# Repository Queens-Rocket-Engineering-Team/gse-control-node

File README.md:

# GSE Control Node

The GSE control node is the control PCB for GSE systems to integrate with launch control. This includes actuator control, fan control, and a load cell reading. This control node is used for control of the GSE equipment on the launch tower.

## System Architecture

Control nodes use an ESP32S3-WROOM-1U microcontroller for systems control. This ESP32S3 communicates with an external control
server to for remote control and data streaming over 2.4GHz WiFi. All commands are sent from the external server, as
control nodes does not autonomously control any systems.

A communications diagram for the GSE control node can be seen below.

```mermaid
---
title: Communications Flow
---
flowchart LR

    ADC(ADS112C04<br>ADCs) <==I2C==> ESP(ESP32 MCU)

    subgraph Controls
        AV(Actuators)
    end

    subgraph Sensors
        LC(Load Cell)
    end

    LC --> ADC

    ESP --> AV

    ESP <-. WiFI .-> WIFI(External Server)
```

## Power Architecture

The GSE control node operates from a 24VDC power supply. The 24V rail is first stepped down to 5.17V with a switching converter and then dropped to 5V and 3.3V with LDOs. The 5V rail supplies analog systems, and the 3.3V rail supplies digital systems. Using LDOs on the switching output allows for low-noise power for analog measurements. There is also a switching converter to step the 24V rail down to 12V, to power fans.

```mermaid
---
title: Power Distribution
---
flowchart LR

    subgraph Actuators
        AV(Actuators)
    end
    24VIN --> AV

    subgraph Voltage Regulation
        BUCK_12([12V Buck])
        BUCK_5.17([5.17V Buck])
        BUCK_5.17 --> 5V([5V LDO])
        BUCK_5.17 --> 3V3([3.3V LDO])
    end

    24VIN --> BUCK_12
    24VIN --> BUCK_5.17

    subgraph Fans
        FANS(Fans)
    end

    subgraph Sensors
        LC(Load Cell)
    end

    BUCK_12 ---> FANS
    5V --> ADC(ADS112C04<br>ADCs)
    3V3 --> ESP(ESP32 MCU)
    3V3 --> ADC
    5V --> LC
```

## Required Software

This project was created using KiCad v10.0. If manufacturing with JLCPCB, install the Fabrication Toolkit KiCad plugin for JLCPCB.

## Recommended Manufacturing Options

If ordering from JLCPCB, use the JLC04161H-3313 stackup option. For JLC PCBA, the standard PCBA option is required due
to the ESP32S3-WROOM-1U being unavailable as a part in the economic PCBA assembly.

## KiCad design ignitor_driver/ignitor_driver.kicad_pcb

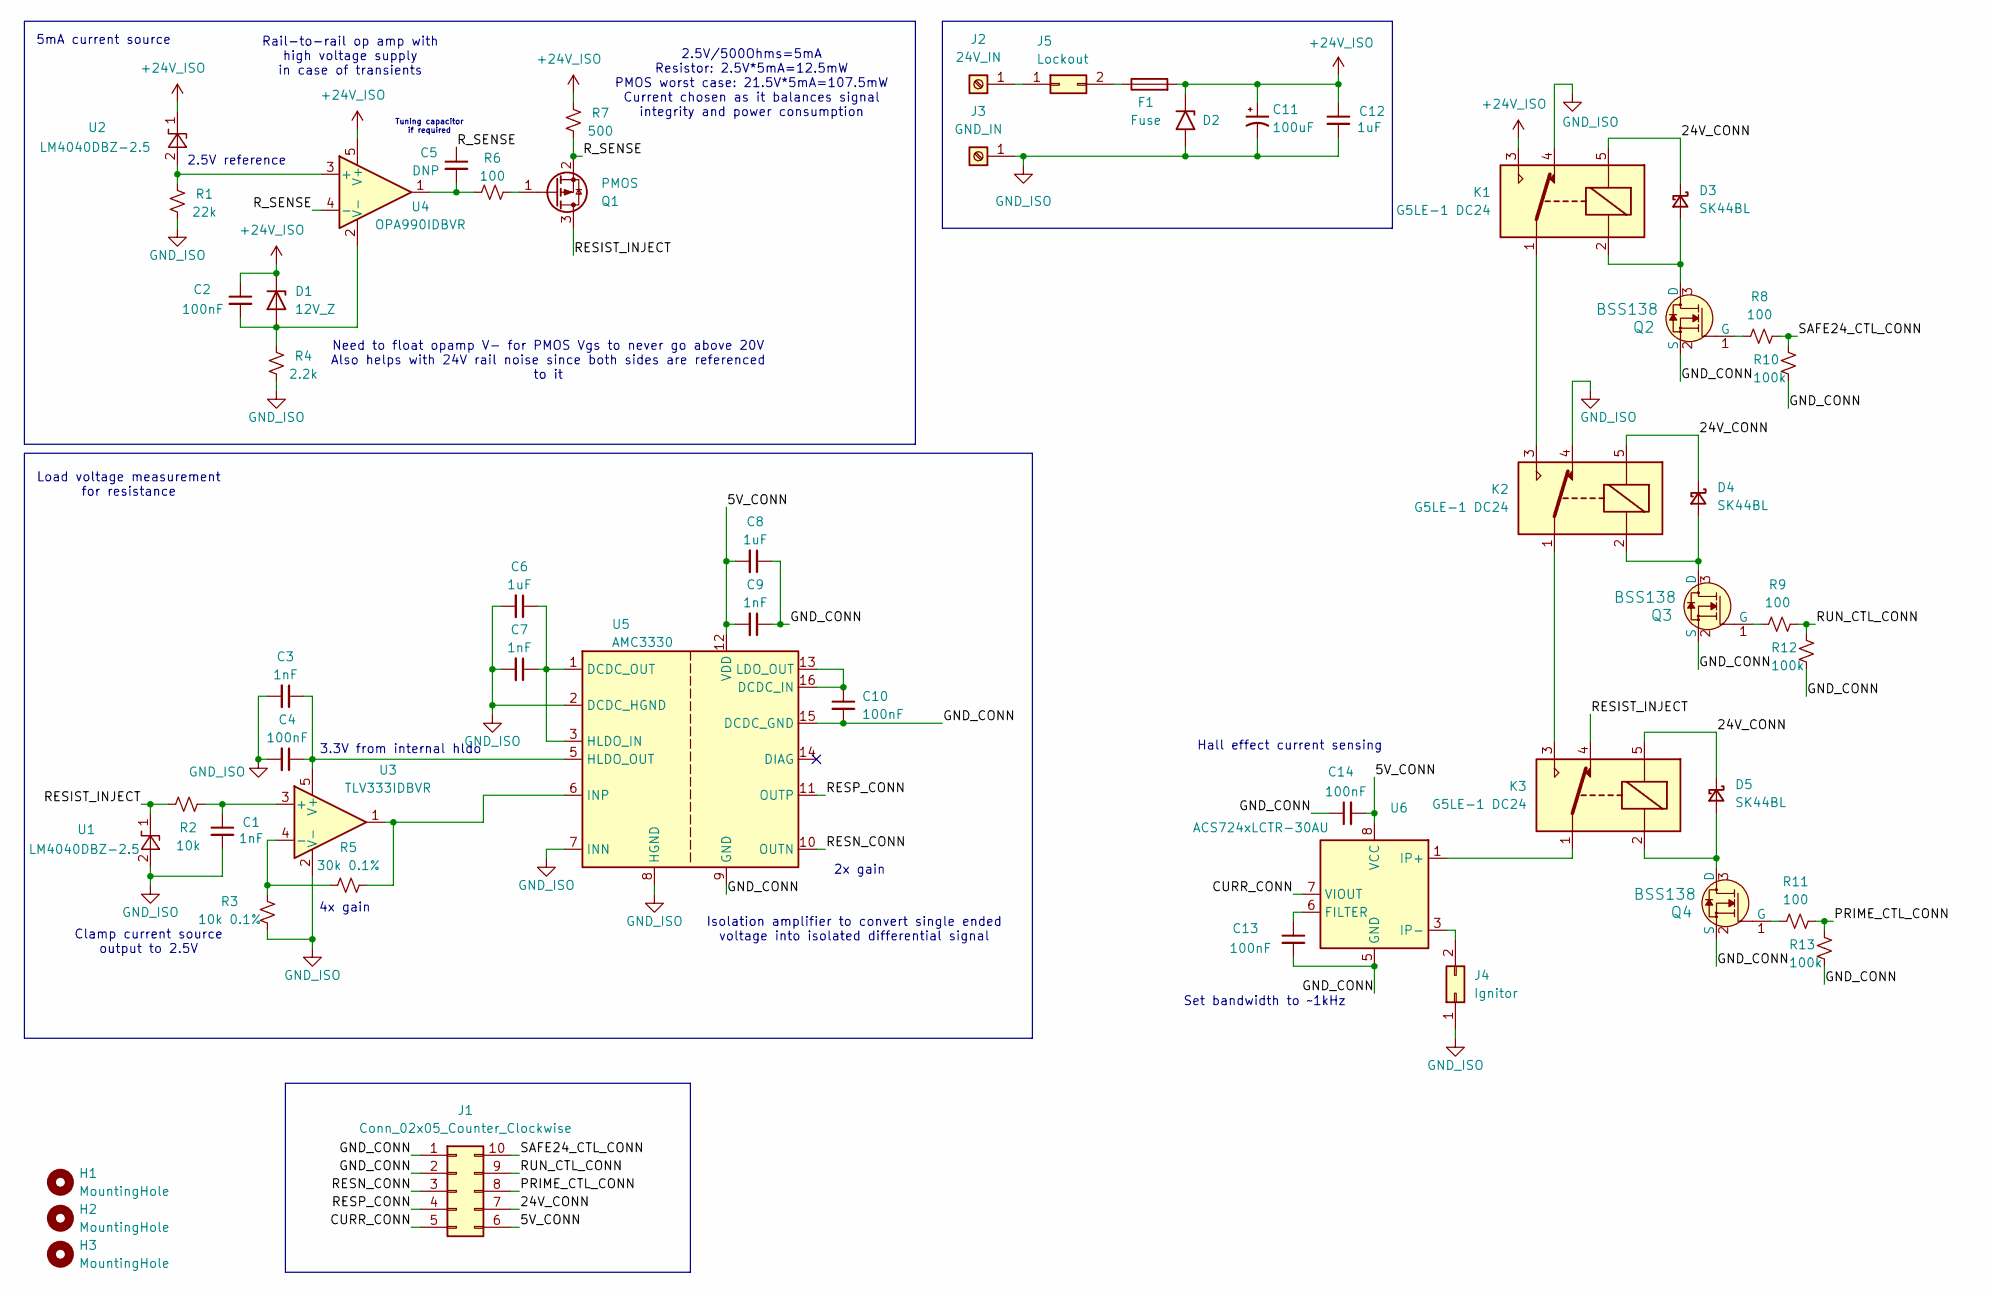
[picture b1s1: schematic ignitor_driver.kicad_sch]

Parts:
C1, C3, C7, C9: 1nF; C_0805_2012Metric_Pad1.18x1.45mm_HandSolder
C2, C4, C10, C13, C14: 100nF; C_0805_2012Metric_Pad1.18x1.45mm_HandSolder
C5: DNP; C_0805_2012Metric_Pad1.18x1.45mm_HandSolder
C6, C8, C12: 1uF; C_0805_2012Metric_Pad1.18x1.45mm_HandSolder
C11: 100uF; CP_Radial_D8.0mm_P5.00mm; MPN EEU-FR1H101B
D1: 12V_Z; D_SOD-123; MPN BZT52C12-13-F
D2: SMCJ26A-13-F; D_SMC; MPN SMCJ26A
D3, D4, D5: SK44BL; D_SMB_Handsoldering; MPN SK44BL-TP
F1: Fuse; Fuseholder_Blade_Mini_Keystone_3568
H1, H2, H3: MountingHole; MountingHole_3.2mm_M3
J1: Conn_02x05_Counter_Clockwise; Molex_Micro-Fit_3.0_43045-1012_2x05_P3.00mm_Vertical
J2: 24V_IN; AMT0440007DB0000G; MPN AMT0440007DB0000G
J3: GND_IN; AMT0440007DB0000G; MPN AMT0440007DB0000G
J4: Ignitor; Molex_Mini-Fit_Jr_5566-02A_2x01_P4.20mm_Vertical
J5: Lockout; Molex_Mini-Fit_Jr_5566-02A_2x01_P4.20mm_Vertical
K1, K2, K3: G5LE-1 DC24; Relay_SPDT_Omron-G5LE-1
Q1: PMOS; SOT-23; MPN BSS83PH6327XTSA1
Q2, Q3, Q4: BSS138; SOT-23; MPN BSS138
R1: 22k; R_0805_2012Metric_Pad1.20x1.40mm_HandSolder; MPN 0402WGF1000TCE
R2: 10k; R_0805_2012Metric_Pad1.20x1.40mm_HandSolder; MPN 0402WGF1000TCE
R3: 10k 0.1%; R_0805_2012Metric_Pad1.20x1.40mm_HandSolder; MPN 0402WGF1000TCE
R4: 2.2k; R_0805_2012Metric_Pad1.20x1.40mm_HandSolder; MPN 0402WGF1000TCE
R5: 30k 0.1%; R_0805_2012Metric_Pad1.20x1.40mm_HandSolder; MPN 0402WGF1000TCE
R6, R8, R9, R11: 100; R_0805_2012Metric_Pad1.20x1.40mm_HandSolder; MPN 0402WGF1000TCE
R7: 500; R_0603_1608Metric_Pad0.98x0.95mm_HandSolder; MPN 0402WGF1000TCE
R10, R12, R13: 100k; R_0805_2012Metric_Pad1.20x1.40mm_HandSolder; MPN 0402WGJ0103TCE
U1, U2: LM4040DBZ-2.5; SOT-23; MPN LM4040C25FTA
U3: TLV333IDBVR; SOT-23-5_HandSoldering
U4: OPA990IDBVR; SOT-23-5_HandSoldering
U5: AMC3330; SOIC-16W_7.5x10.3mm_P1.27mm; MPN AMC3330DWER
U6: ACS724xLCTR-30AU; SOIC-8_3.9x4.9mm_P1.27mm; MPN ACS724LLCTR-30AU-T

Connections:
+24V_ISO: C2.1, C11.1, C12.1, D1.1 (K), D2.1 (A1), F1.2, K1.3, R7.1, U2.1 (K), U4.5 (V+)
/5V_CONN: C8.2, C9.2, C14.2, J1.6, U5.12 (VDD), U6.8 (VCC)
/24V_CONN: D3.1 (K), D4.1 (K), D5.1 (K), J1.7, K1.5, K2.5, K3.5
/CURR_CONN: J1.5, U6.7 (VIOUT)
/GND_CONN: C8.1, C9.1, C10.2, C13.2, C14.1, J1.1, J1.2, Q2.2 (S), Q3.2 (S), Q4.2 (S), R10.2, R12.2, R13.2, U5.9 (GND), U5.15 (DCDC_GND), U6.5 (GND)
/PRIME_CTL_CONN: J1.8, R11.2, R13.1
/RESIST_INJECT: K3.4, Q1.3 (D), R2.1, U1.1 (K)
/RESN_CONN: J1.3, U5.10 (OUTN)
/RESP_CONN: J1.4, U5.11 (OUTP)
/RUN_CTL_CONN: J1.9, R9.2, R12.1
/R_SENSE: C5.1, Q1.2 (S), R7.2, U4.4 (-)
/SAFE24_CTL_CONN: J1.10, R8.2, R10.1
GND_ISO: C1.2, C3.2, C4.2, C6.2, C7.2, C11.2, C12.2, D2.2 (A2), J3.1 (Pin_1_1), J4.1, K1.4, K2.4, R1.2, R3.1, R4.2, U1.2 (A), U3.2 (V-), U5.2 (DCDC_HGND), U5.7 (INN), U5.8 (HGND)
unnamed: C5.2, R6.1, U4.1
unnamed: C2.2, D1.2 (A), R4.1, U4.2 (V-)
unnamed: D3.2 (A), K1.2, Q2.3 (D)
unnamed: D4.2 (A), K2.2, Q3.3 (D)
unnamed: D5.2 (A), K3.2, Q4.3 (D)
unnamed: J2.1 (Pin_1_1), J5.1
unnamed: J4.2, U6.3 (IP-), U6.4 (IP-)
unnamed: F1.1, J5.2
unnamed: K1.1, K2.3
unnamed: K2.1, K3.3
unnamed: K3.1, U6.1 (IP+), U6.2 (IP+)
unnamed: Q1.1 (G), R6.2
unnamed: Q2.1 (G), R8.1
unnamed: Q3.1 (G), R9.1
unnamed: Q4.1 (G), R11.1
unnamed: R1.1, U2.2 (A), U4.3 (+)
unnamed: C1.1, R2.2, U3.3 (+)
unnamed: R3.2, R5.1, U3.4 (-)
unnamed: C3.1, C4.1, U3.5 (V+), U5.5 (HLDO_OUT)
unnamed: C10.1, U5.13 (LDO_OUT), U5.16 (DCDC_IN)
unnamed: C6.1, C7.1, U5.1 (DCDC_OUT), U5.3 (HLDO_IN)
unnamed: R5.2, U3.1, U5.6 (INP)
unnamed: C13.1, U6.6 (FILTER)

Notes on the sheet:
5mA current source
Hall effect current sensing
4x gain
Clamp current source output to 2.5V
Need to float opamp V- for PMOS Vgs to never go above 20V Also helps with 24V rail noise since both sides are referenced to it
Load voltage measurement for resistance
2.5V/500Ohms=5mA Resistor: 2.5V*5mA=12.5mW PMOS worst case: 21.5V*5mA=107.5mW Current chosen as it balances signal integrity and power consumption
Rail-to-rail op amp with high voltage supply in case of transients
2x gain
Isolation amplifier to convert single ended voltage into isolated differential signal
Tuning capacitor if required
Set bandwidth to ~1kHz
2.5V reference
3.3V from internal hldo

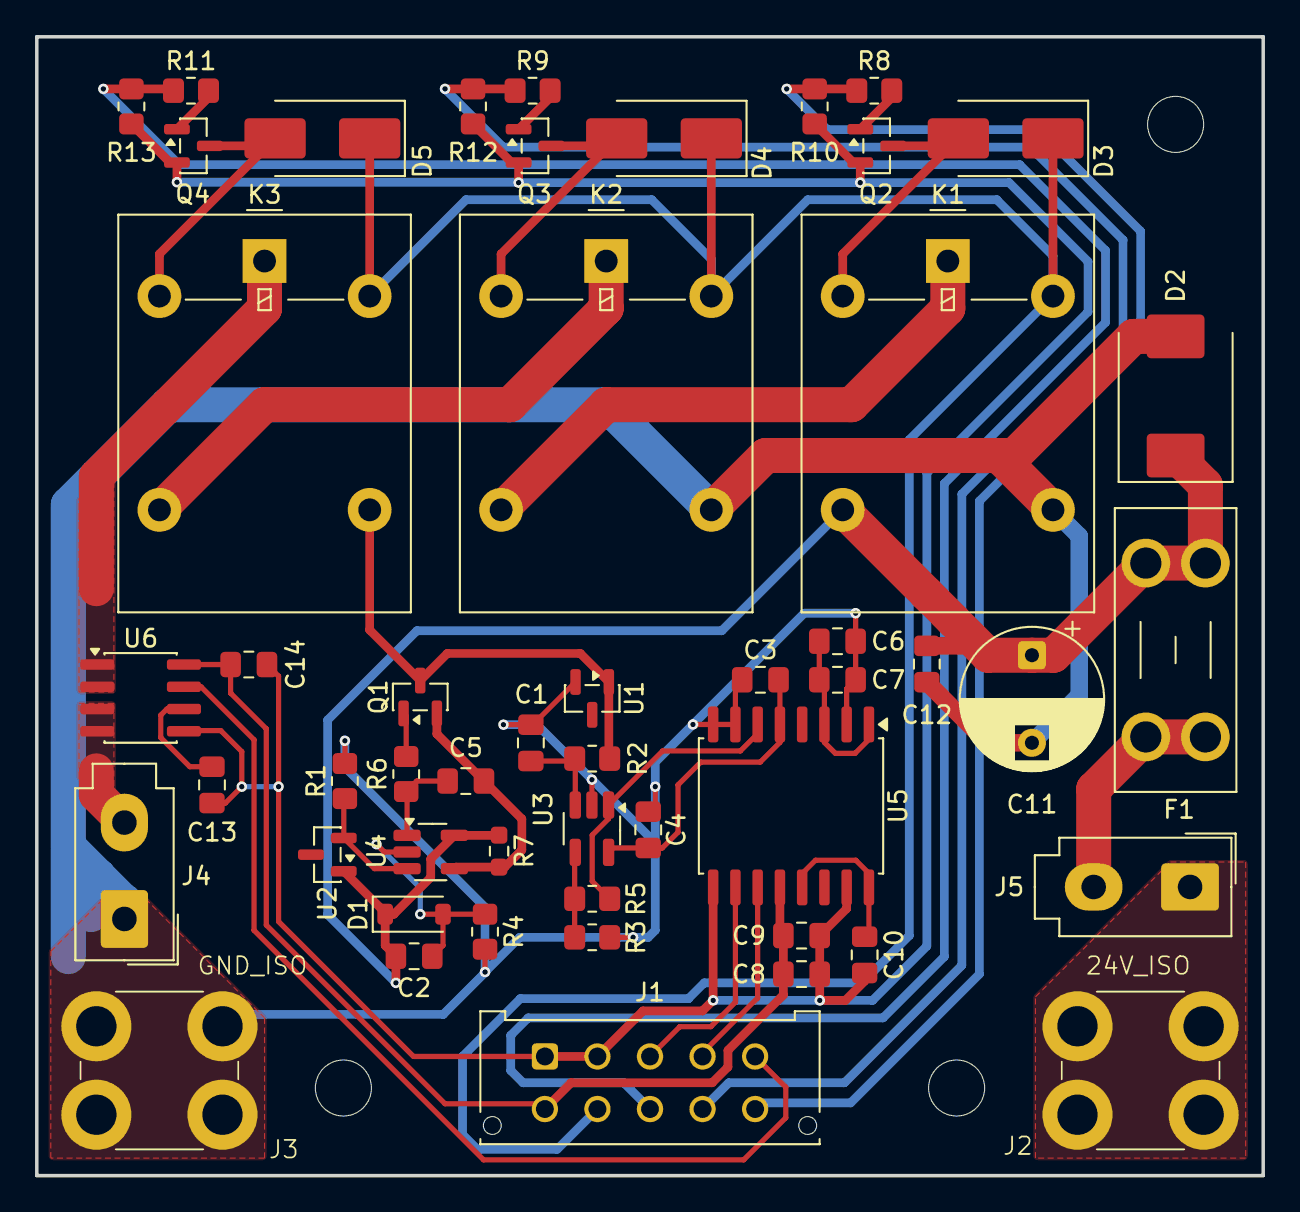
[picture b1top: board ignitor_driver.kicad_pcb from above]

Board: 2 copper layers, 70.0 x 65.0 mm, 54 parts (0 on the bottom side), 36 nets.

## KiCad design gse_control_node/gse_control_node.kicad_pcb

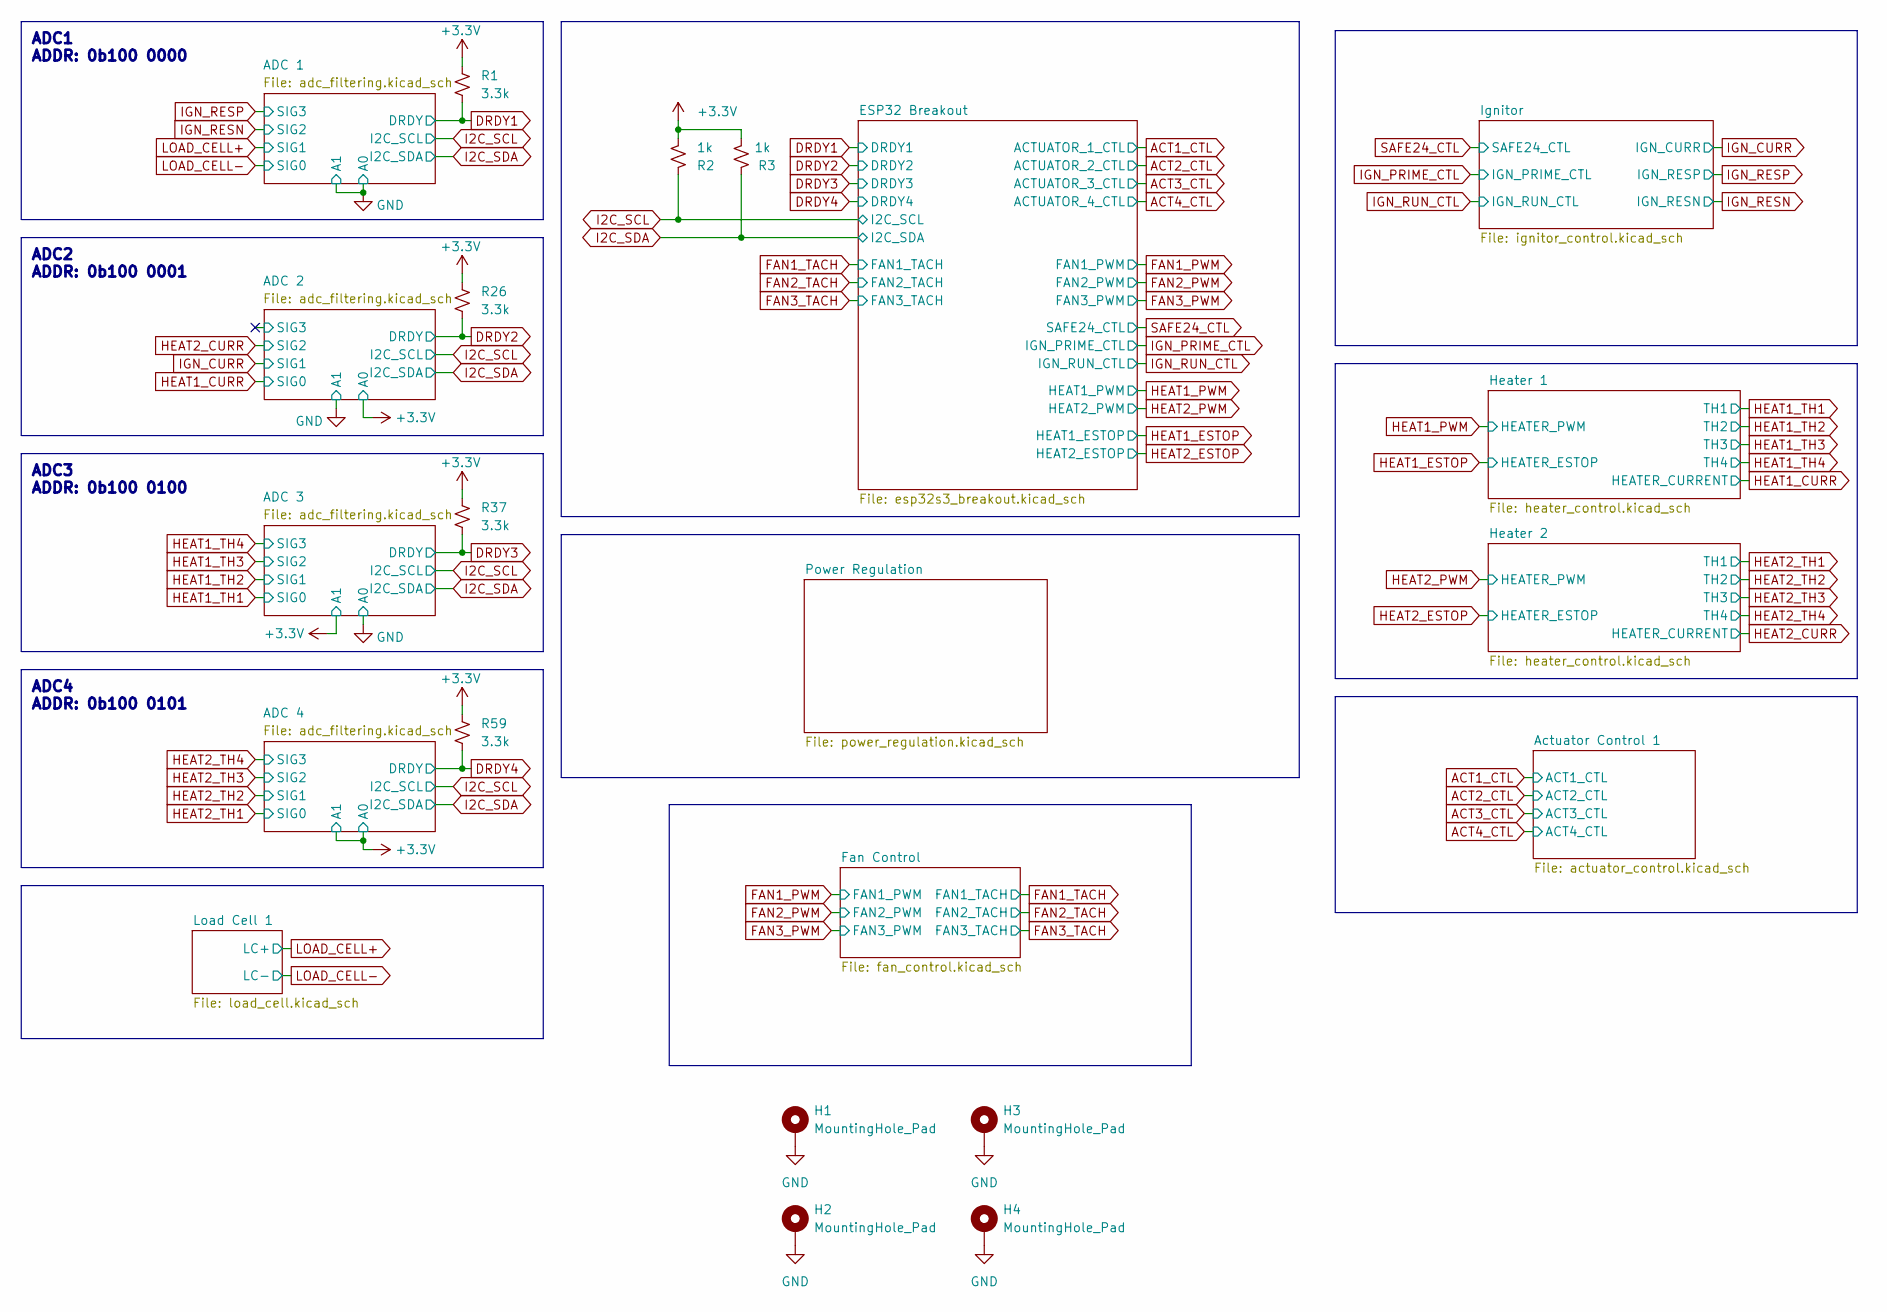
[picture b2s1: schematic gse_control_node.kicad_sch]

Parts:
H1, H2, H3, H4: MountingHole_Pad; MountingHole_3.2mm_M3_ISO7380_Pad; LCSC N/A
R1, R26, R37, R59: 3.3k; R_0603_1608Metric; LCSC C22978
R2, R3: 1k; R_0603_1608Metric; LCSC C21190

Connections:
+3.3V: R1.1, R2.2, R3.2, R26.1, R37.1, R59.1; also elsewhere on the board
DRDY1: R1.2; also elsewhere on the board
DRDY2: R26.2; also elsewhere on the board
DRDY3: R37.2; also elsewhere on the board
DRDY4: R59.2; also elsewhere on the board
GND: H1.1 (1_1), H2.1 (1_1), H3.1 (1_1), H4.1 (1_1); also elsewhere on the board
I2C_SCL: R2.1; also elsewhere on the board
I2C_SDA: R3.1; also elsewhere on the board

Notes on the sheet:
ADC2 ADDR: 0b100 0001
ADC4 ADDR: 0b100 0101
ADC1 ADDR: 0b100 0000
ADC3 ADDR: 0b100 0100

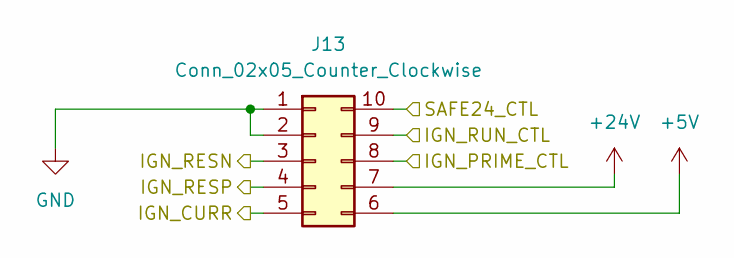
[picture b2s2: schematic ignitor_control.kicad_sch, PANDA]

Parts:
J13: Conn_02x05_Counter_Clockwise; Molex_Micro-Fit_3.0_43045-1012_2x05_P3.00mm_Vertical

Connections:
+5V: J13.6; also elsewhere on the board
+24V: J13.7; also elsewhere on the board
GND: J13.1, J13.2; also elsewhere on the board
IGN_CURR: J13.5; also elsewhere on the board
IGN_PRIME_CTL: J13.8; also elsewhere on the board
IGN_RESN: J13.3; also elsewhere on the board
IGN_RESP: J13.4; also elsewhere on the board
IGN_RUN_CTL: J13.9; also elsewhere on the board
SAFE24_CTL: J13.10; also elsewhere on the board

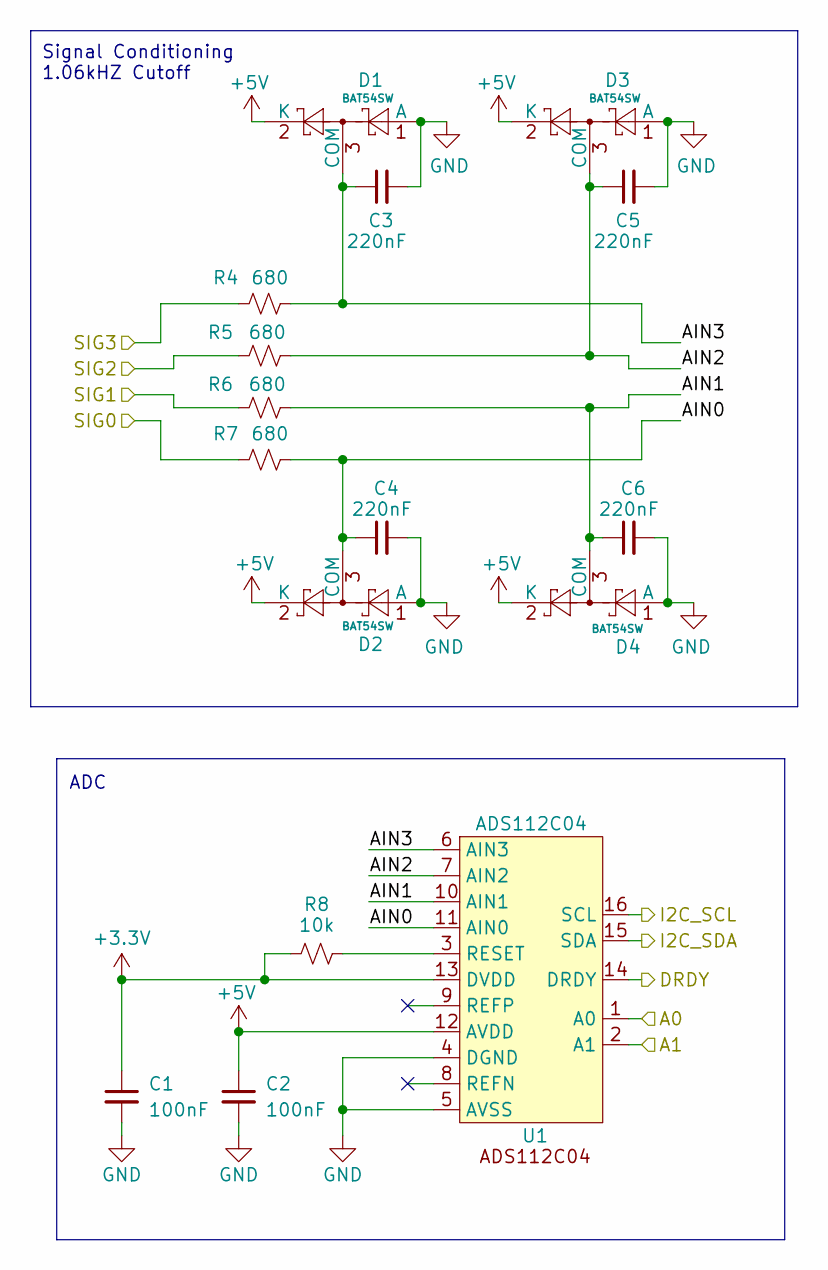
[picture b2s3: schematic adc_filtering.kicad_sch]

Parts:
C1, C2: 100nF; C_0402_1005Metric; LCSC C307331
C3, C4, C5, C6: 220nF; C_0402_1005Metric; LCSC C16772
D1, D2, D3, D4: BAT54SW; SOT-323_SC-70; LCSC C83575
R4, R5, R6, R7: 680; R_0603_1608Metric; LCSC C23228
R8: 10k; R_0603_1608Metric; LCSC C25804
U1: ADS112C04; TSSOP-16_4.4x5mm_P0.65mm; LCSC C701615

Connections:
+3.3V: C1.1, R8.1, U1.13 (DVDD); also elsewhere on the board
+5V: C2.1, D1.2 (K), D2.2 (K), D3.2 (K), D4.2 (K), U1.12 (AVDD); also elsewhere on the board
/ADC 1/AIN0: C4.1, D2.3 (COM), R7.2, U1.11 (AIN0)
/ADC 1/AIN1: C6.1, D4.3 (COM), R6.2, U1.10 (AIN1)
/ADC 1/AIN2: C5.1, D3.3 (COM), R5.2, U1.7 (AIN2)
/ADC 1/AIN3: C3.1, D1.3 (COM), R4.2, U1.6 (AIN3)
DRDY1: U1.14 (DRDY); also elsewhere on the board
GND: C1.2, C2.2, C3.2, C4.2, C5.2, C6.2, D1.1 (A), D2.1 (A), D3.1 (A), D4.1 (A), U1.1 (A0), U1.2 (A1), U1.4 (DGND), U1.5 (AVSS); also elsewhere on the board
I2C_SCL: U1.16 (SCL); also elsewhere on the board
I2C_SDA: U1.15 (SDA); also elsewhere on the board
IGN_RESN: R5.1; also elsewhere on the board
IGN_RESP: R4.1; also elsewhere on the board
LOAD_CELL+: R6.1; also elsewhere on the board
LOAD_CELL-: R7.1; also elsewhere on the board
unnamed: R8.2, U1.3 (RESET)

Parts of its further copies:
C37, C38, C43, C44, C49, C50: 100nF; C_0402_1005Metric; LCSC C307331
C39, C40, C41, C42, C45, C46, C47, C48, C51, C52, C53, C54: 220nF; C_0402_1005Metric; LCSC C16772
D12, D13, D14, D16, D17, D18, D20, D21, D22, D24, D25, D26: BAT54SW; SOT-323_SC-70; LCSC C83575
R27, R28, R29, R30, R49, R50, R51, R55, R60, R61, R62, R63: 680; R_0603_1608Metric; LCSC C23228
R31, R56, R64: 10k; R_0603_1608Metric; LCSC C25804
U8, U9, U10: ADS112C04; TSSOP-16_4.4x5mm_P0.65mm; LCSC C701615

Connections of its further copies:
+3.3V: C37.1, C43.1, C49.1, R31.1, R56.1, R64.1, U8.1 (A0), U8.13 (DVDD), U9.2 (A1), U9.13 (DVDD), U10.1 (A0), U10.2 (A1), U10.13 (DVDD); also elsewhere on the board
+5V: C38.1, C44.1, C50.1, D12.2 (K), D13.2 (K), D14.2 (K), D16.2 (K), D17.2 (K), D18.2 (K), D20.2 (K), D21.2 (K), D22.2 (K), D24.2 (K), D25.2 (K), D26.2 (K), U8.12 (AVDD), U9.12 (AVDD), U10.12 (AVDD); also elsewhere on the board
/ADC 2/AIN0: C40.1, D13.3 (COM), R30.2, U8.11 (AIN0)
/ADC 2/AIN1: C42.1, D16.3 (COM), R29.2, U8.10 (AIN1)
/ADC 2/AIN2: C41.1, D14.3 (COM), R28.2, U8.7 (AIN2)
/ADC 2/AIN3: C39.1, D12.3 (COM), R27.2, U8.6 (AIN3)
/ADC 2/SIG3: R27.1
/ADC 3/AIN0: C46.1, D18.3 (COM), R55.2, U9.11 (AIN0)
/ADC 3/AIN1: C48.1, D21.3 (COM), R51.2, U9.10 (AIN1)
/ADC 3/AIN2: C47.1, D20.3 (COM), R50.2, U9.7 (AIN2)
/ADC 3/AIN3: C45.1, D17.3 (COM), R49.2, U9.6 (AIN3)
/ADC 4/AIN0: C52.1, D24.3 (COM), R63.2, U10.11 (AIN0)
/ADC 4/AIN1: C54.1, D26.3 (COM), R62.2, U10.10 (AIN1)
/ADC 4/AIN2: C53.1, D25.3 (COM), R61.2, U10.7 (AIN2)
/ADC 4/AIN3: C51.1, D22.3 (COM), R60.2, U10.6 (AIN3)
DRDY2: U8.14 (DRDY); also elsewhere on the board
DRDY3: U9.14 (DRDY); also elsewhere on the board
DRDY4: U10.14 (DRDY); also elsewhere on the board
GND: C37.2, C38.2, C39.2, C40.2, C41.2, C42.2, C43.2, C44.2, C45.2, C46.2, C47.2, C48.2, C49.2, C50.2, C51.2, C52.2, C53.2, C54.2, D12.1 (A), D13.1 (A), D14.1 (A), D16.1 (A), D17.1 (A), D18.1 (A), D20.1 (A), D21.1 (A), D22.1 (A), D24.1 (A), D25.1 (A), D26.1 (A), U8.2 (A1), U8.4 (DGND), U8.5 (AVSS), U9.1 (A0), U9.4 (DGND), U9.5 (AVSS), U10.4 (DGND), U10.5 (AVSS); also elsewhere on the board
HEAT1_CURR: R30.1; also elsewhere on the board
HEAT1_TH1: R55.1; also elsewhere on the board
HEAT1_TH2: R51.1; also elsewhere on the board
HEAT1_TH3: R50.1; also elsewhere on the board
HEAT1_TH4: R49.1; also elsewhere on the board
HEAT2_CURR: R28.1; also elsewhere on the board
HEAT2_TH1: R63.1; also elsewhere on the board
HEAT2_TH2: R62.1; also elsewhere on the board
HEAT2_TH3: R61.1; also elsewhere on the board
HEAT2_TH4: R60.1; also elsewhere on the board
I2C_SCL: U8.16 (SCL), U9.16 (SCL), U10.16 (SCL); also elsewhere on the board
I2C_SDA: U8.15 (SDA), U9.15 (SDA), U10.15 (SDA); also elsewhere on the board
IGN_CURR: R29.1; also elsewhere on the board
unnamed: R31.2, U8.3 (RESET)
unnamed: R56.2, U9.3 (RESET)
unnamed: R64.2, U10.3 (RESET)

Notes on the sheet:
ADC
Signal Conditioning 1.06kHZ Cutoff

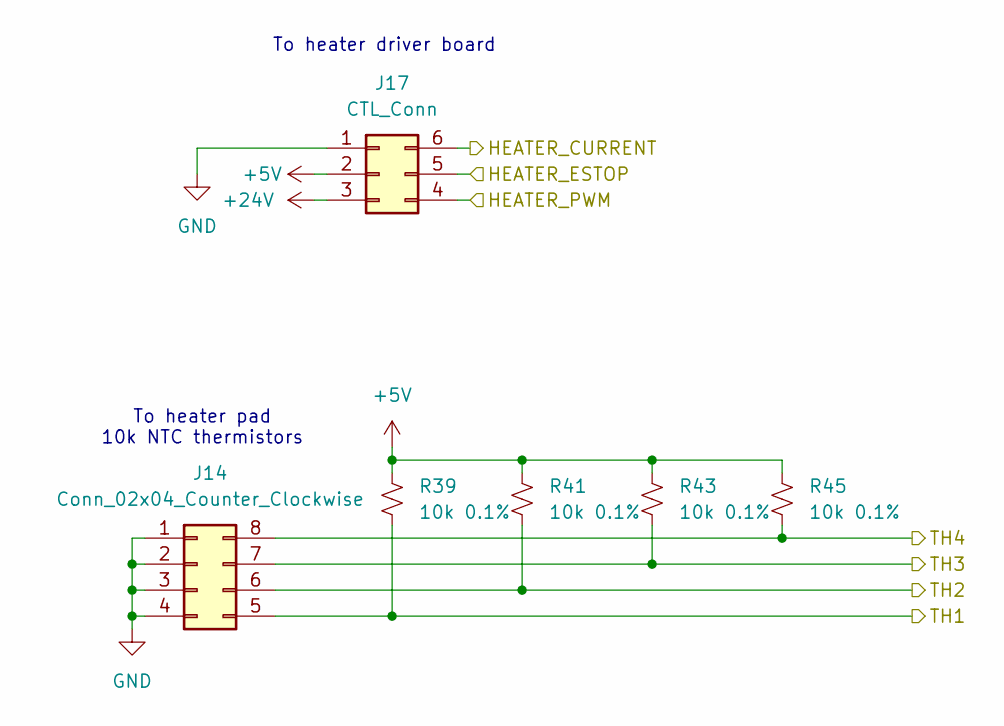
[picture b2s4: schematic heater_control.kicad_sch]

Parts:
J14: Conn_02x04_Counter_Clockwise; Molex_Micro-Fit_3.0_43045-0812_2x04_P3.00mm_Vertical
J17: CTL_Conn; Molex_Micro-Fit_3.0_43045-0612_2x03_P3.00mm_Vertical
R39, R41, R43, R45: 10k 0.1%; R_0603_1608Metric

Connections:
+5V: J17.2, R39.1, R41.1, R43.1, R45.1; also elsewhere on the board
+24V: J17.3; also elsewhere on the board
GND: J14.1, J14.2, J14.3, J14.4, J17.1; also elsewhere on the board
HEAT2_CURR: J17.6; also elsewhere on the board
HEAT2_ESTOP: J17.5; also elsewhere on the board
HEAT2_PWM: J17.4; also elsewhere on the board
HEAT2_TH1: J14.5, R39.2; also elsewhere on the board
HEAT2_TH2: J14.6, R41.2; also elsewhere on the board
HEAT2_TH3: J14.7, R43.2; also elsewhere on the board
HEAT2_TH4: J14.8, R45.2; also elsewhere on the board

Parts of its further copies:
J12: Conn_02x04_Counter_Clockwise; Molex_Micro-Fit_3.0_43045-0812_2x04_P3.00mm_Vertical
J16: CTL_Conn; Molex_Micro-Fit_3.0_43045-0612_2x03_P3.00mm_Vertical
R38, R40, R42, R44: 10k 0.1%; R_0603_1608Metric

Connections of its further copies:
+5V: J16.2, R38.1, R40.1, R42.1, R44.1; also elsewhere on the board
+24V: J16.3; also elsewhere on the board
GND: J12.1, J12.2, J12.3, J12.4, J16.1; also elsewhere on the board
HEAT1_CURR: J16.6; also elsewhere on the board
HEAT1_ESTOP: J16.5; also elsewhere on the board
HEAT1_PWM: J16.4; also elsewhere on the board
HEAT1_TH1: J12.5, R38.2; also elsewhere on the board
HEAT1_TH2: J12.6, R40.2; also elsewhere on the board
HEAT1_TH3: J12.7, R42.2; also elsewhere on the board
HEAT1_TH4: J12.8, R44.2; also elsewhere on the board

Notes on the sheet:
To heater driver board
To heater pad 10k NTC thermistors

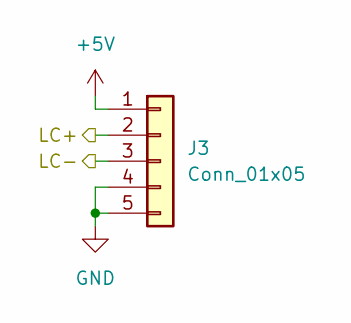
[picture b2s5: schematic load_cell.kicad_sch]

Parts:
J3: Conn_01x05; Molex_Micro-Fit_3.0_43650-0515_1x05_P3.00mm_Vertical; LCSC N/A

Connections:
+5V: J3.1; also elsewhere on the board
GND: J3.4, J3.5; also elsewhere on the board
LOAD_CELL+: J3.2; also elsewhere on the board
LOAD_CELL-: J3.3; also elsewhere on the board

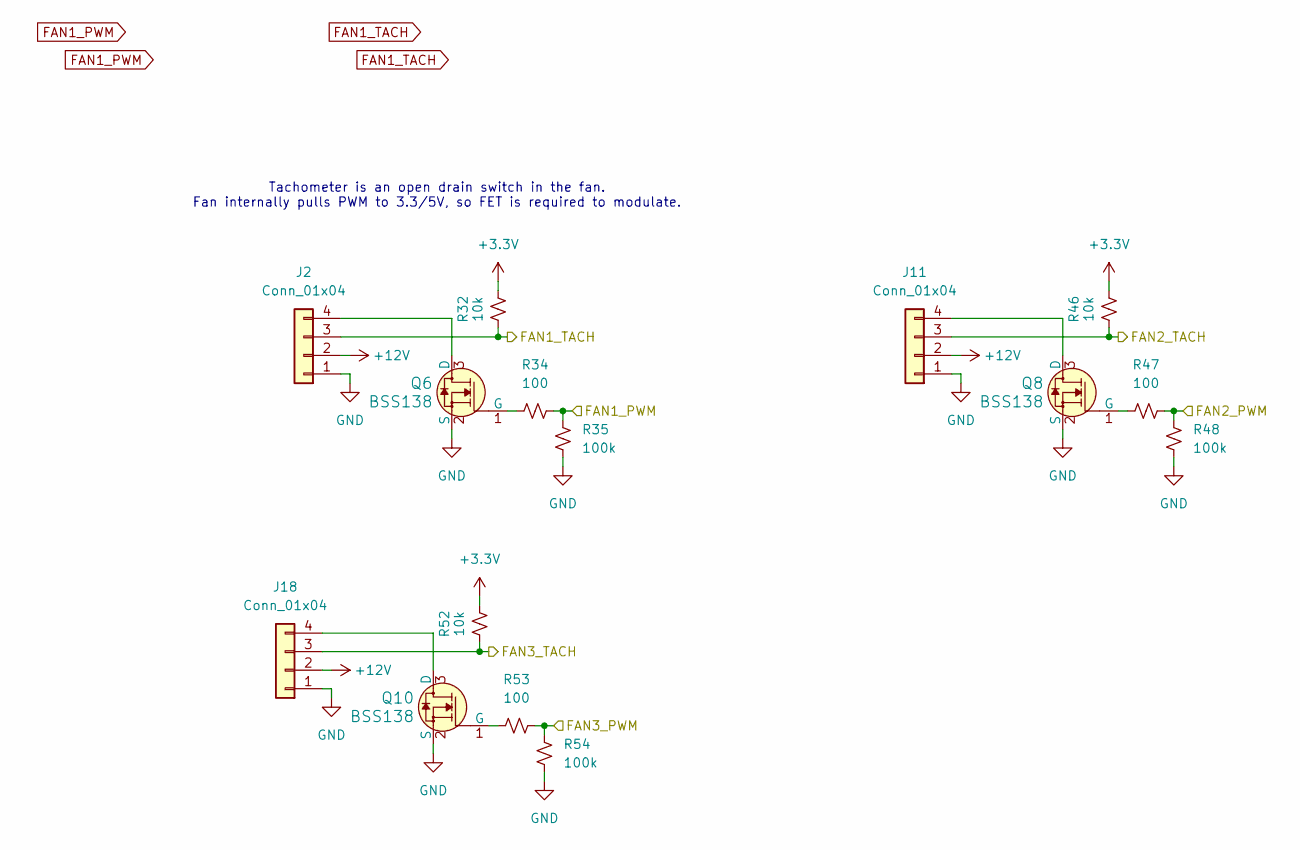
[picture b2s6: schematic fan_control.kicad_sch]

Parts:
J2, J11, J18: Conn_01x04; Molex_KK-254_AE-6410-04A_1x04_P2.54mm_Vertical; LCSC N/A
Q6, Q8, Q10: BSS138; SOT-23-3; LCSC C82045
R32, R46, R52: 10k; R_0603_1608Metric; LCSC C25804
R34, R47, R53: 100; R_0603_1608Metric
R35, R48, R54: 100k; R_0603_1608Metric; LCSC C122538

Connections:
+3.3V: R32.2, R46.2, R52.2; also elsewhere on the board
+12V: J2.2, J11.2, J18.2; also elsewhere on the board
FAN1_PWM: R34.2, R35.1; also elsewhere on the board
FAN1_TACH: J2.3, R32.1; also elsewhere on the board
FAN2_PWM: R47.2, R48.1; also elsewhere on the board
FAN2_TACH: J11.3, R46.1; also elsewhere on the board
FAN3_PWM: R53.2, R54.1; also elsewhere on the board
FAN3_TACH: J18.3, R52.1; also elsewhere on the board
GND: J2.1, J11.1, J18.1, Q6.2 (S), Q8.2 (S), Q10.2 (S), R35.2, R48.2, R54.2; also elsewhere on the board
unnamed: J2.4, Q6.3 (D)
unnamed: J11.4, Q8.3 (D)
unnamed: J18.4, Q10.3 (D)
unnamed: Q6.1 (G), R34.1
unnamed: Q8.1 (G), R47.1
unnamed: Q10.1 (G), R53.1

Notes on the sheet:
Tachometer is an open drain switch in the fan. Fan internally pulls PWM to 3.3/5V, so FET is required to modulate.

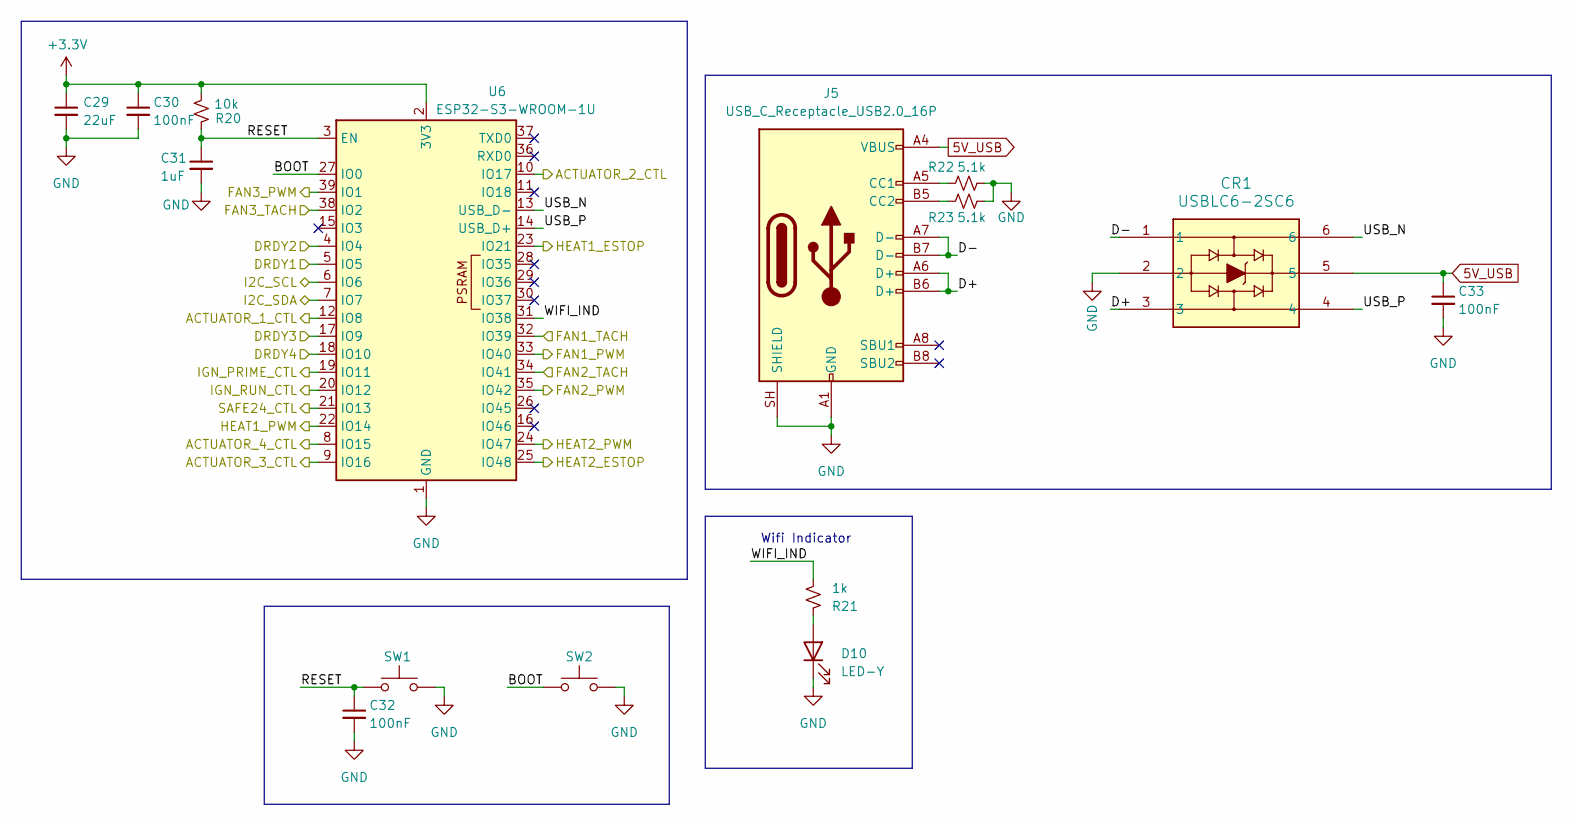
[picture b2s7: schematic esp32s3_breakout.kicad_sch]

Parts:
C29: 22uF; C_0805_2012Metric; LCSC C45783
C30, C32, C33: 100nF; C_0402_1005Metric; LCSC C307331
C31: 1uF; C_0603_1608Metric; LCSC C15849
CR1: USBLC6-2SC6; SOT-23-6; LCSC C7519
D10: LED-Y; LED_0805_2012Metric; LCSC C2296
J5: USB_C_Receptacle_USB2.0_16P; USB_C_Receptacle_G-Switch_GT-USB-7051x; LCSC C2843970
R20: 10k; R_0603_1608Metric; LCSC C25804
R21: 1k; R_0603_1608Metric; LCSC C21190
R22, R23: 5.1k; R_0603_1608Metric
SW1, SW2: USAKRO UK-B0227-G4.3-B-250; SW_Tactile_SPST_NO_Straight_CK_PTS636Sx25SMTRLFS; LCSC C556661
U6: ESP32-S3-WROOM-1U; LCSC C2913202

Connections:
5V_USB: C33.1, CR1.5, J5.A4 (VBUS), J5.A9 (VBUS), J5.B4 (VBUS), J5.B9 (VBUS); also elsewhere on the board
+3.3V: C29.1, C30.1, R20.2, U6.2 (3V3); also elsewhere on the board
/ESP32 Breakout/BOOT: SW2.1, U6.27 (IO0)
/ESP32 Breakout/D+: CR1.3, J5.A6 (D+), J5.B6 (D+)
/ESP32 Breakout/D-: CR1.1, J5.A7 (D-), J5.B7 (D-)
/ESP32 Breakout/RESET: C31.1, C32.1, R20.1, SW1.1, U6.3 (EN)
/ESP32 Breakout/USB_N: CR1.6, U6.13 (USB_D-)
/ESP32 Breakout/USB_P: CR1.4, U6.14 (USB_D+)
/ESP32 Breakout/WIFI_IND: R21.2, U6.31 (IO38)
ACT1_CTL: U6.12 (IO8); also elsewhere on the board
ACT2_CTL: U6.10 (IO17); also elsewhere on the board
ACT3_CTL: U6.9 (IO16); also elsewhere on the board
ACT4_CTL: U6.8 (IO15); also elsewhere on the board
DRDY1: U6.5 (IO5); also elsewhere on the board
DRDY2: U6.4 (IO4); also elsewhere on the board
DRDY3: U6.17 (IO9); also elsewhere on the board
DRDY4: U6.18 (IO10); also elsewhere on the board
FAN1_PWM: U6.33 (IO40); also elsewhere on the board
FAN1_TACH: U6.32 (IO39); also elsewhere on the board
FAN2_PWM: U6.35 (IO42); also elsewhere on the board
FAN2_TACH: U6.34 (IO41); also elsewhere on the board
FAN3_PWM: U6.39 (IO1); also elsewhere on the board
FAN3_TACH: U6.38 (IO2); also elsewhere on the board
GND: C29.2, C30.2, C31.2, C32.2, C33.2, CR1.2, D10.1 (K), J5.A1 (GND), J5.A12 (GND), J5.B1 (GND), J5.B12 (GND), J5.SH (SHIELD), R22.2, R23.2, SW1.2, SW2.2, U6.1 (GND), U6.40 (GND), U6.41 (GND); also elsewhere on the board
HEAT1_ESTOP: U6.23 (IO21); also elsewhere on the board
HEAT1_PWM: U6.22 (IO14); also elsewhere on the board
HEAT2_ESTOP: U6.25 (IO48); also elsewhere on the board
HEAT2_PWM: U6.24 (IO47); also elsewhere on the board
I2C_SCL: U6.6 (IO6); also elsewhere on the board
I2C_SDA: U6.7 (IO7); also elsewhere on the board
IGN_PRIME_CTL: U6.19 (IO11); also elsewhere on the board
IGN_RUN_CTL: U6.20 (IO12); also elsewhere on the board
unnamed: D10.2 (A), R21.1
unnamed: J5.A5 (CC1), R22.1
unnamed: J5.B5 (CC2), R23.1
SAFE24_CTL: U6.21 (IO13); also elsewhere on the board

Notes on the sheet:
Wifi Indicator
